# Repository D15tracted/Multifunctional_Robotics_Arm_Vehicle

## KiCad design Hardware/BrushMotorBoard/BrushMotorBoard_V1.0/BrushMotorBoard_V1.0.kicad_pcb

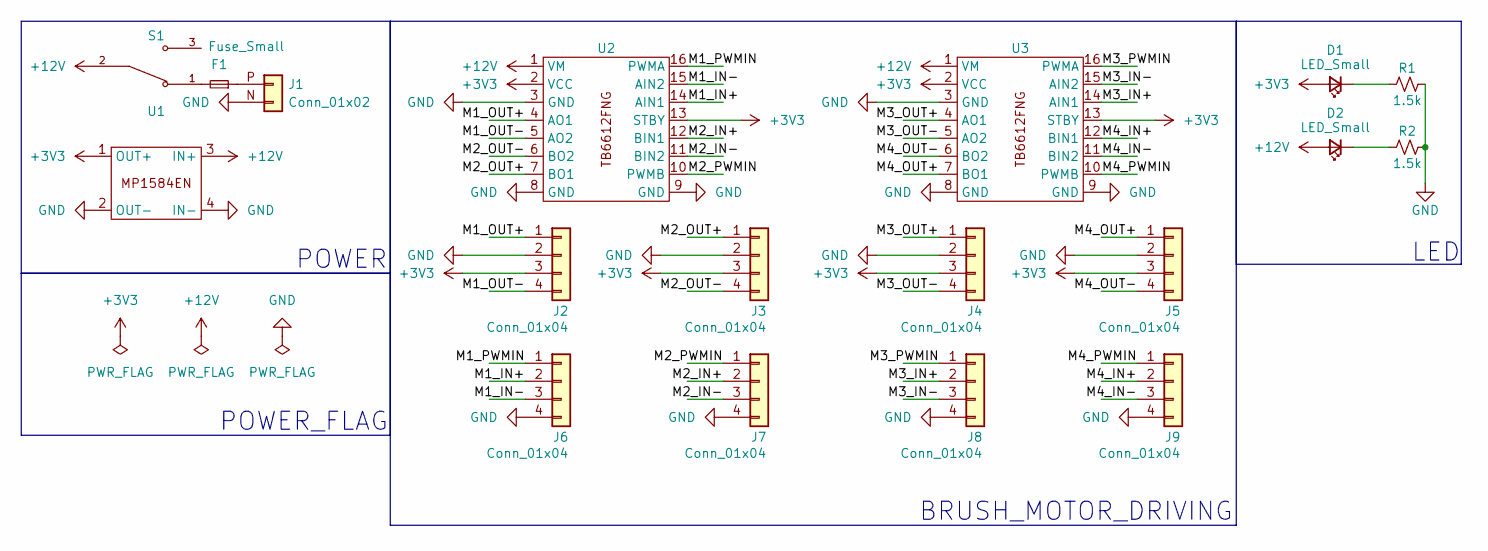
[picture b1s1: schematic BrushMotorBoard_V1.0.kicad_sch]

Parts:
D1, D2: LED_Small; LED_0805_2012Metric
F1: Fuse_Small; Fuse_Blade_ATO_directSolder
J1: Conn_01x02; AMASS_XT60-M
J2, J3, J4, J5, J6, J7, J8, J9: Conn_01x04; JST_XH_B4B-XH-A_1x04_P2.50mm_Vertical
R1, R2: 1.5k; R_0805_2012Metric
S1: SS12D10
U1: MP1584EN
U2, U3: TB6612FNG_Module

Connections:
+3V3: D1.2 (A), J2.3, J3.3, J4.3, J5.3, U1.1 (OUT+), U2.2 (VCC), U2.13 (STBY), U3.2 (VCC), U3.13 (STBY)
+12V: D2.2 (A), S1.2, U1.3 (IN+), U2.1 (VM), U3.1 (VM)
/M1_IN+: J6.2, U2.14 (AIN1)
/M1_IN-: J6.3, U2.15 (AIN2)
/M1_OUT+: J2.1, U2.4 (AO1)
/M1_OUT-: J2.4, U2.5 (AO2)
/M1_PWMIN: J6.1, U2.16 (PWMA)
/M2_IN+: J7.2, U2.12 (BIN1)
/M2_IN-: J7.3, U2.11 (BIN2)
/M2_OUT+: J3.1, U2.7 (BO1)
/M2_OUT-: J3.4, U2.6 (BO2)
/M2_PWMIN: J7.1, U2.10 (PWMB)
/M3_IN+: J8.2, U3.14 (AIN1)
/M3_IN-: J8.3, U3.15 (AIN2)
/M3_OUT+: J4.1, U3.4 (AO1)
/M3_OUT-: J4.4, U3.5 (AO2)
/M3_PWMIN: J8.1, U3.16 (PWMA)
/M4_IN+: J9.2, U3.12 (BIN1)
/M4_IN-: J9.3, U3.11 (BIN2)
/M4_OUT+: J5.1, U3.7 (BO1)
/M4_OUT-: J5.4, U3.6 (BO2)
/M4_PWMIN: J9.1, U3.10 (PWMB)
GND: J1.N (Pin_2), J2.2, J3.2, J4.2, J5.2, J6.4, J7.4, J8.4, J9.4, R1.2, R2.2, U1.2 (OUT-), U1.4 (IN-), U2.3 (GND), U2.8 (GND), U2.9 (GND), U3.3 (GND), U3.8 (GND), U3.9 (GND)
unnamed: D1.1 (K), R1.1
unnamed: D2.1 (K), R2.1
unnamed: F1.2, S1.1
unnamed: F1.1, J1.P (Pin_1)

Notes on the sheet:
POWER_FLAG
BRUSH_MOTOR_DRIVING
LED
POWER

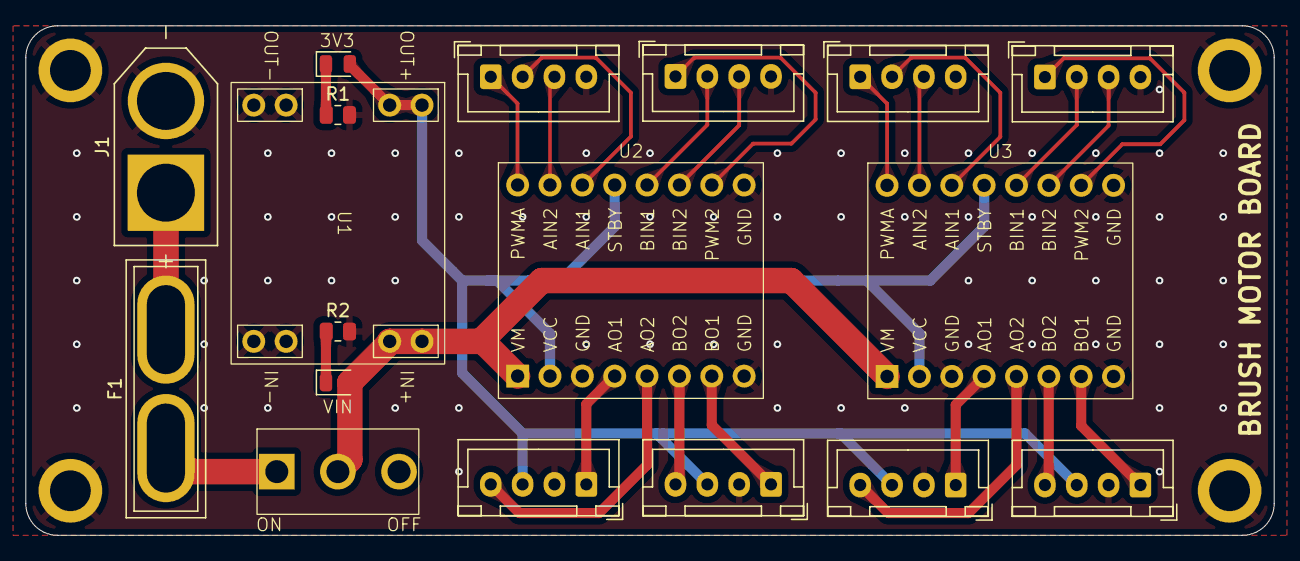
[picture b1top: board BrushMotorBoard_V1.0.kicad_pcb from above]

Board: 2 copper layers, 98.0 x 40.0 mm, 18 parts (0 on the bottom side), 27 nets.

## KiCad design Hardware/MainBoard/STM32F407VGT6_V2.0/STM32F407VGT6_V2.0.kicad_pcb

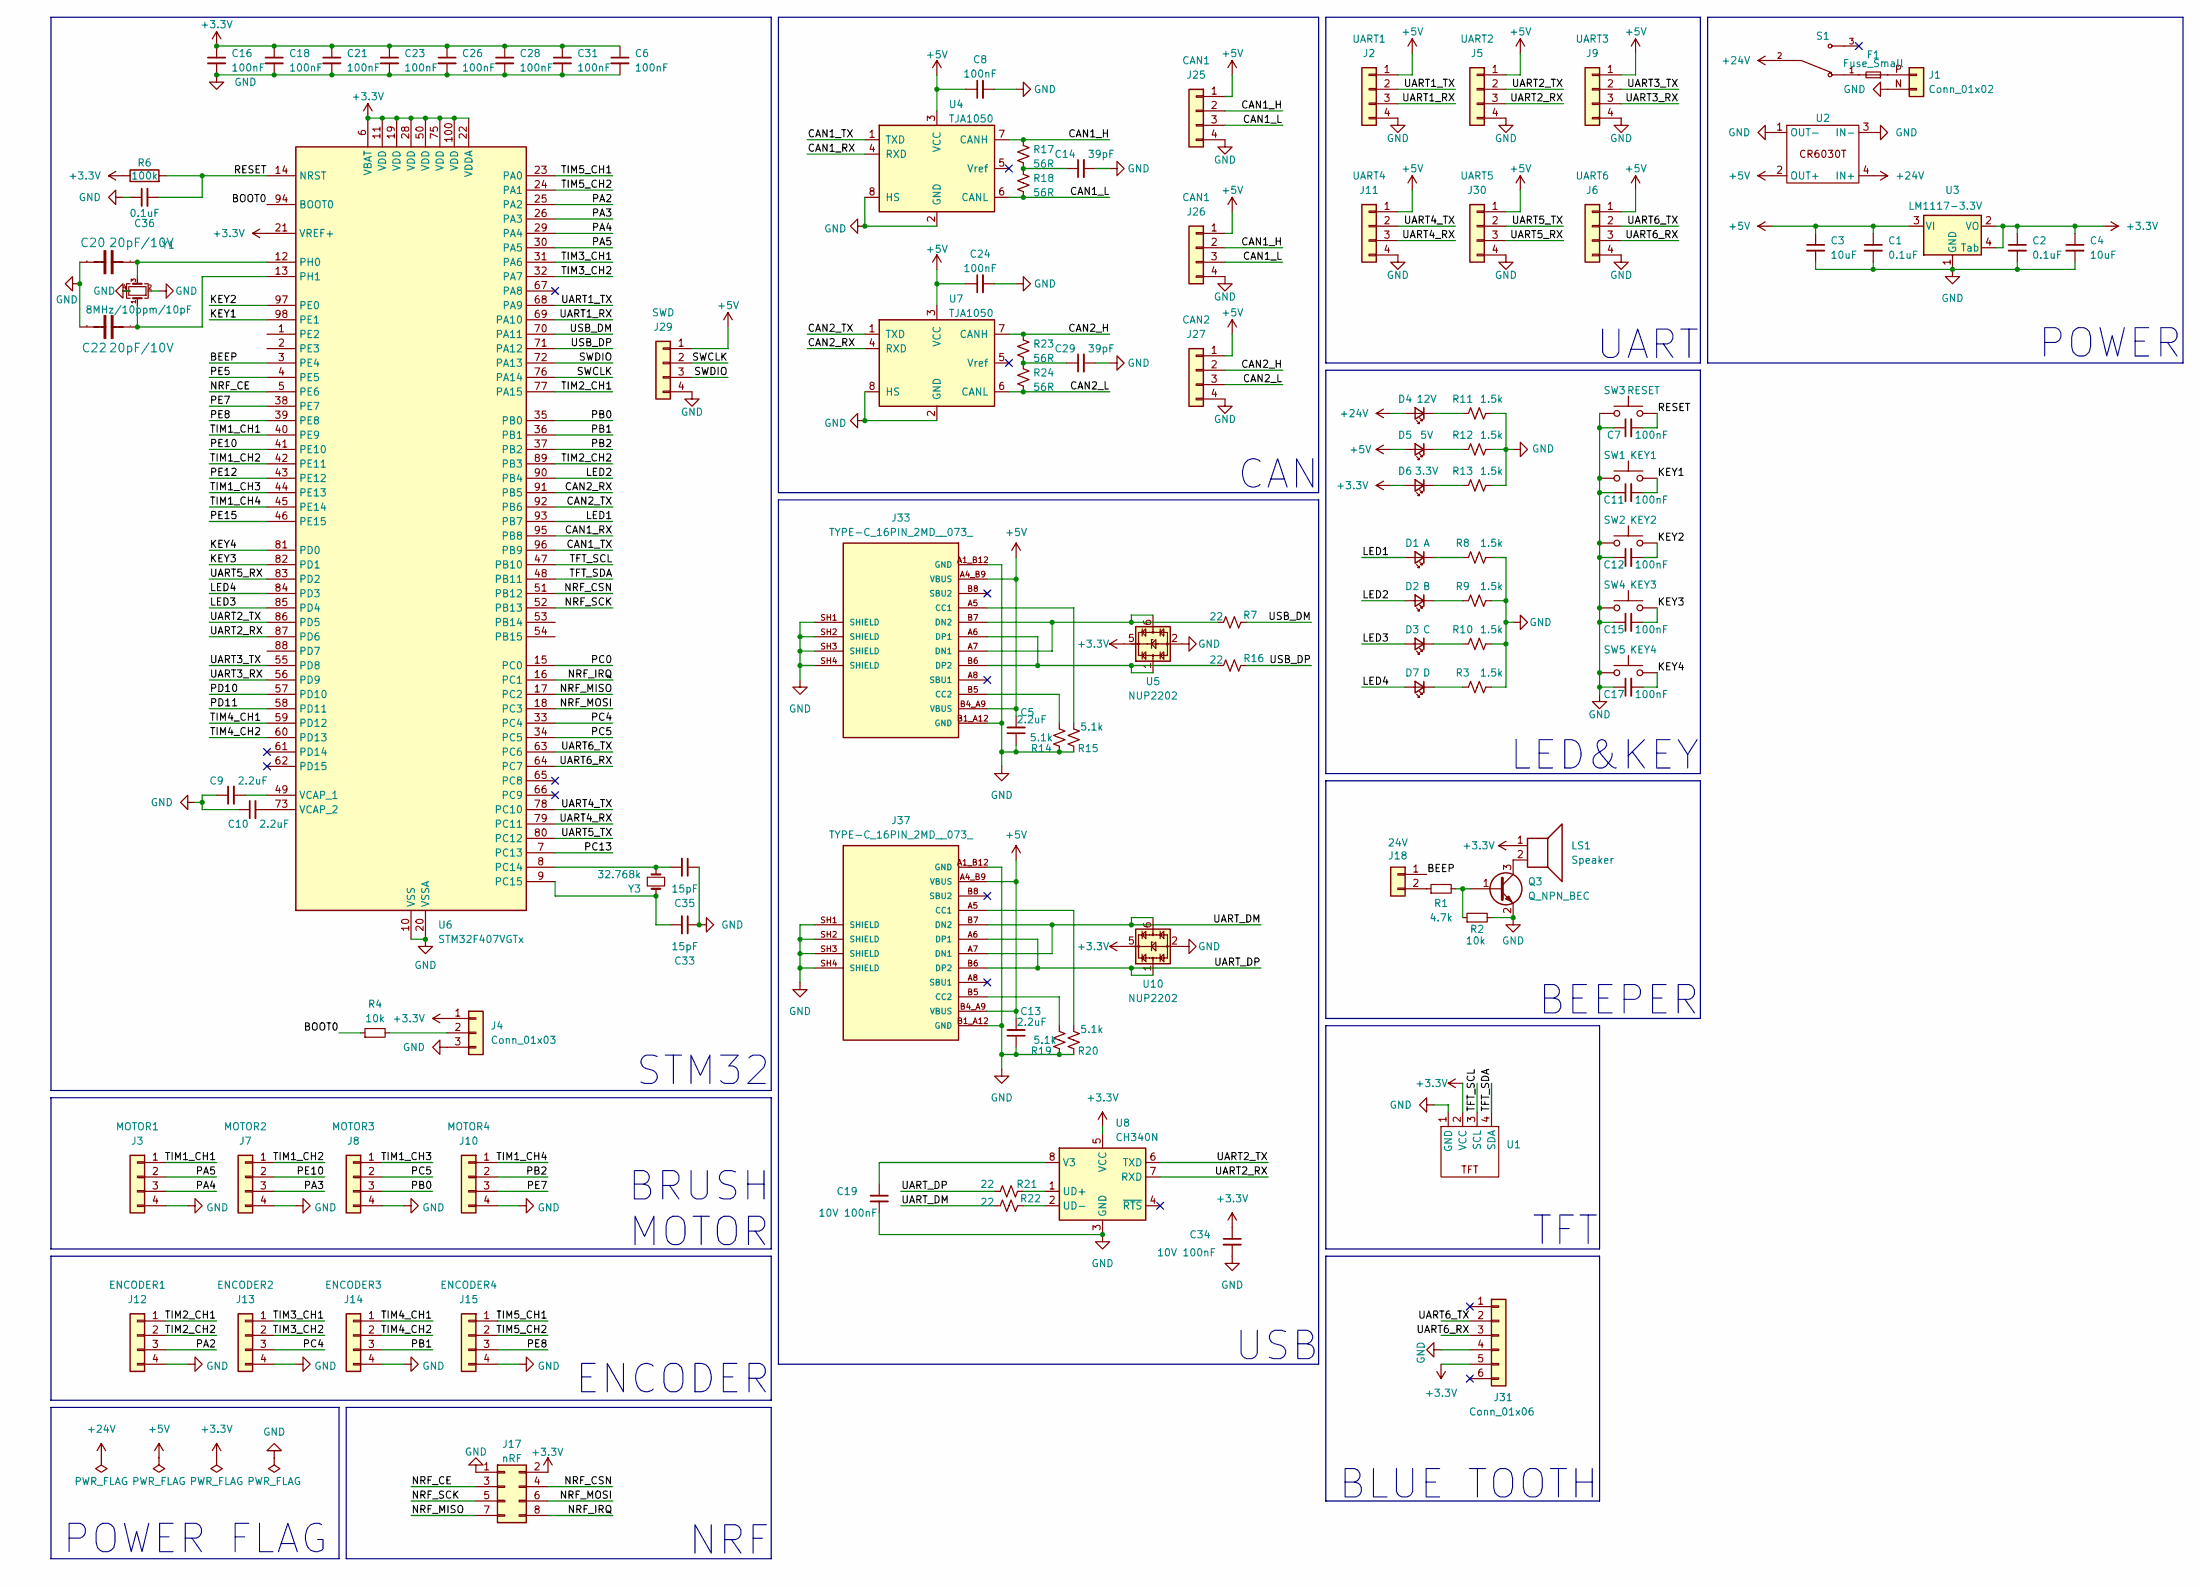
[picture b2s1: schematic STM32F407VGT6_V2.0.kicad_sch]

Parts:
C1, C2, C36: 0.1uF; C_0603_1608Metric
C3, C4: 10uF; C_0603_1608Metric
C5, C9, C10, C13: 2.2uF; C_0603_1608Metric
C6, C7, C8, C11, C12, C15, C16, C17, C18, C21, C23, C24, C26, C28, C31: 100nF; C_0603_1608Metric
C14, C29: 39pF; C_0603_1608Metric
C19, C34: 10V 100nF; C_0603_1608Metric
C20, C22: 20pF/10V; C_0603_1608Metric
C33, C35: 15pF; C_0603_1608Metric
D1: A; LED_0603_1608Metric
D2: B; LED_0603_1608Metric
D3: C; LED_0603_1608Metric
D4: 12V; LED_0603_1608Metric
D5: 5V; LED_0603_1608Metric
D6: 3.3V; LED_0603_1608Metric
D7: D; LED_0603_1608Metric
F1: Fuse_Small; Fuse_Blade_ATO_directSolder
J1: Conn_01x02; AMASS_XT60-M
J2: UART1; JST_XH_B4B-XH-A_1x04_P2.50mm_Vertical
J3: MOTOR1; JST_XH_B4B-XH-A_1x04_P2.50mm_Vertical
J4: Conn_01x03; PinHeader_1x03_P2.54mm_Vertical
J5: UART2; JST_XH_B4B-XH-A_1x04_P2.50mm_Vertical
J6: UART6; JST_XH_B4B-XH-A_1x04_P2.50mm_Vertical
J7: MOTOR2; JST_XH_B4B-XH-A_1x04_P2.50mm_Vertical
J8: MOTOR3; JST_XH_B4B-XH-A_1x04_P2.50mm_Vertical
J9: UART3; JST_XH_B4B-XH-A_1x04_P2.50mm_Vertical
J10: MOTOR4; JST_XH_B4B-XH-A_1x04_P2.50mm_Vertical
J11: UART4; JST_XH_B4B-XH-A_1x04_P2.50mm_Vertical
J12: ENCODER1; JST_XH_B4B-XH-A_1x04_P2.50mm_Vertical
J13: ENCODER2; JST_XH_B4B-XH-A_1x04_P2.50mm_Vertical
J14: ENCODER3; JST_XH_B4B-XH-A_1x04_P2.50mm_Vertical
J15: ENCODER4; JST_XH_B4B-XH-A_1x04_P2.50mm_Vertical
J17: nRF; PinHeader_2x04_P2.54mm_Vertical
J18: 24V; Conn1x02P
J25, J26: CAN1; JST_XH_B4B-XH-A_1x04_P2.50mm_Vertical
J27: CAN2; JST_XH_B4B-XH-A_1x04_P2.50mm_Vertical
J29: SWD; JST_XH_B4B-XH-A_1x04_P2.50mm_Vertical
J30: UART5; JST_XH_B4B-XH-A_1x04_P2.50mm_Vertical
J31: Conn_01x06; BLUE_TOOTH
J33, J37: TYPE-C_16PIN_2MD__073_; SHOUHAN_ TYPEC 16PIN; PARTREV A
LS1: Speaker; Beeper9mm
Q3: Q_NPN_BEC; SOT-23
R1: 4.7k; R_0603_1608Metric
R2, R4: 10k; R_0603_1608Metric
R3, R8, R9, R10, R11, R12, R13: 1.5k; R_0603_1608Metric
R6: 100k; R_0603_1608Metric
R7, R16, R21, R22: 22; R_0603_1608Metric
R14, R15, R19, R20: 5.1k; R_0603_1608Metric
R17, R18, R23, R24: 56R; R_0603_1608Metric
S1: SS12D10
SW1: KEY1; SW_Push
SW2: KEY2; SW_Push
SW3: RESET; SW_Push
SW4: KEY3; SW_Push
SW5: KEY4; SW_Push
U1: OLED_WithoutMountingHole
U2: CR6030T
U3: LM1117-3.3V; SOT-223
U4, U7: TJA1050; ISO1541D_SOIC-8
U5, U10: NUP2202; SOT-363_SC-70-6
U6: STM32F407VGTx; LQFP-100_14x14mm_P0.5mm
U8: CH340N; SOIC-8_5.3x6.2mm_P1.27mm
Y1: 8MHz/10ppm/10pF; Crystal_SMD_3225-4Pin_3.2x2.5mm
Y3: 32.768k; SMD-3215-2P

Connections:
+3.3V: C2.1, C4.1, C6.1, C16.1, C18.1, C21.1, C23.1, C26.1, C28.1, C31.1, C34.1, D6.2 (A), J4.1, J17.2, J31.5, LS1.1, R6.1, U1.2 (VCC), U3.2 (VO), U3.4 (Tab), U5.5, U6.6 (VBAT), U6.11 (VDD), U6.19 (VDD), U6.21 (VREF+), U6.22 (VDDA), U6.28 (VDD), U6.50 (VDD), U6.75 (VDD), U6.100 (VDD), U8.5 (VCC), U10.5
+5V: C1.1, C3.1, C5.2, C8.1, C13.2, C24.1, D5.2 (A), J2.1, J5.1, J6.1, J9.1, J11.1, J25.1, J26.1, J27.1, J29.1, J30.1, J33.A4_B9 (VBUS), J33.B4_A9 (VBUS), J37.A4_B9 (VBUS), J37.B4_A9 (VBUS), U2.2 (OUT+), U3.3 (VI), U4.3 (VCC), U7.3 (VCC)
+24V: D4.2 (A), S1.2, U2.4 (IN+)
/BEEP: J18.1, U6.3 (PE4)
/BOOT0: R4.1, U6.94 (BOOT0)
/CAN1_H: J25.2, J26.2, R17.1, U4.7 (CANH)
/CAN1_L: J25.3, J26.3, R18.2, U4.6 (CANL)
/CAN1_RX: U4.4 (RXD), U6.95 (PB8)
/CAN1_TX: U4.1 (TXD), U6.96 (PB9)
/CAN2_H: J27.2, R23.1, U7.7 (CANH)
/CAN2_L: J27.3, R24.2, U7.6 (CANL)
/CAN2_RX: U6.91 (PB5), U7.4 (RXD)
/CAN2_TX: U6.92 (PB6), U7.1 (TXD)
/KEY1: C11.2, SW1.2, U6.98 (PE1)
/KEY2: C12.2, SW2.2, U6.97 (PE0)
/KEY3: C15.2, SW4.2, U6.82 (PD1)
/KEY4: C17.2, SW5.2, U6.81 (PD0)
/LED1: D1.2 (A), U6.93 (PB7)
/LED2: D2.2 (A), U6.90 (PB4)
/LED3: D3.2 (A), U6.85 (PD4)
/LED4: D7.2 (A), U6.84 (PD3)
/NRF_CE: J17.3, U6.5 (PE6)
/NRF_CSN: J17.4, U6.51 (PB12)
/NRF_IRQ: J17.8, U6.16 (PC1)
/NRF_MISO: J17.7, U6.17 (PC2)
/NRF_MOSI: J17.6, U6.18 (PC3)
/NRF_SCK: J17.5, U6.52 (PB13)
/PA2: J12.3, U6.25 (PA2)
/PA3: J7.3, U6.26 (PA3)
/PA4: J3.3, U6.29 (PA4)
/PA5: J3.2, U6.30 (PA5)
/PB0: J8.3, U6.35 (PB0)
/PB1: J14.3, U6.36 (PB1)
/PB2: J10.2, U6.37 (PB2)
/PC0: U6.15 (PC0)
/PC4: J13.3, U6.33 (PC4)
/PC5: J8.2, U6.34 (PC5)
/PC13: U6.7 (PC13)
/PD10: U6.57 (PD10)
/PD11: U6.58 (PD11)
/PE5: U6.4 (PE5)
/PE7: J10.3, U6.38 (PE7)
/PE8: J15.3, U6.39 (PE8)
/PE10: J7.2, U6.41 (PE10)
/PE12: U6.43 (PE12)
/PE15: U6.46 (PE15)
/RESET: C7.2, C36.2, R6.2, SW3.2, U6.14 (NRST)
/SWCLK: J29.2, U6.76 (PA14)
/SWDIO: J29.3, U6.72 (PA13)
/TFT_SCL: U1.3 (SCL), U6.47 (PB10)
/TFT_SDA: U1.4 (SDA), U6.48 (PB11)
/TIM1_CH1: J3.1, U6.40 (PE9)
/TIM1_CH2: J7.1, U6.42 (PE11)
/TIM1_CH3: J8.1, U6.44 (PE13)
/TIM1_CH4: J10.1, U6.45 (PE14)
/TIM2_CH1: J12.1, U6.77 (PA15)
/TIM2_CH2: J12.2, U6.89 (PB3)
/TIM3_CH1: J13.1, U6.31 (PA6)
/TIM3_CH2: J13.2, U6.32 (PA7)
/TIM4_CH1: J14.1, U6.59 (PD12)
/TIM4_CH2: J14.2, U6.60 (PD13)
/TIM5_CH1: J15.1, U6.23 (PA0)
/TIM5_CH2: J15.2, U6.24 (PA1)
/UART1_RX: J2.3, U6.69 (PA10)
/UART1_TX: J2.2, U6.68 (PA9)
/UART2_RX: J5.3, U6.87 (PD6), U8.7 (RXD)
/UART2_TX: J5.2, U6.86 (PD5), U8.6 (TXD)
/UART3_RX: J9.3, U6.56 (PD9)
/UART3_TX: J9.2, U6.55 (PD8)
/UART4_RX: J11.3, U6.79 (PC11)
/UART4_TX: J11.2, U6.78 (PC10)
/UART5_RX: J30.3, U6.83 (PD2)
/UART5_TX: J30.2, U6.80 (PC12)
/UART6_RX: J6.3, J31.3, U6.64 (PC7)
/UART6_TX: J6.2, J31.2, U6.63 (PC6)
/UART_DM: J37.A7 (DN1), J37.B7 (DN2), R22.1, U10.6
/UART_DP: J37.A6 (DP1), J37.B6 (DP2), R21.1, U10.1
/USB_DM: R7.2, U6.70 (PA11)
/USB_DP: R16.2, U6.71 (PA12)
GND: C1.2, C2.2, C3.2, C4.2, C5.1, C6.2, C7.1, C8.2, C9.1, C10.1, C11.1, C12.1, C13.1, C14.2, C15.1, C16.2, C17.1, C18.2, C19.2, C20.1, C21.2, C22.1, C23.2, C24.2, C26.2, C28.2, C29.2, C31.2, C33.1, C34.2, C35.1, C36.1, J1.N (Pin_2), J2.4, J3.4, J4.3, J5.4, J6.4, J7.4, J8.4, J9.4, J10.4, J11.4, J12.4, J13.4, J14.4, J15.4, J17.1, J25.4, J26.4, J27.4, J29.4, J30.4, J31.4, J33.A1_B12 (GND), J33.B1_A12 (GND), J33.SH1 (SHIELD), J33.SH2 (SHIELD), J33.SH3 (SHIELD), J33.SH4 (SHIELD), J37.A1_B12 (GND), J37.B1_A12 (GND), J37.SH1 (SHIELD), J37.SH2 (SHIELD), J37.SH3 (SHIELD), J37.SH4 (SHIELD), Q3.2 (E), R2.2, R3.1, R8.1, R9.1, R10.1, R11.1, R12.1, R13.1, R14.2, R15.2, R19.2, R20.2, SW1.1, SW2.1, SW3.1, SW4.1, SW5.1, U1.1 (GND), U2.1 (OUT-), U2.3 (IN-), U3.1 (GND), U4.2 (GND), U4.8 (HS), U5.2, U6.10 (VSS), U6.20 (VSSA), U6.27 (VSS), U6.74 (VSS), U6.99 (VSS), U7.2 (GND), U7.8 (HS), U8.3 (GND), U10.2, Y1.2, Y1.4
unnamed: C14.1, R17.2, R18.1
unnamed: C29.1, R23.2, R24.1
unnamed: D1.1 (K), R8.2
unnamed: D2.1 (K), R9.2
unnamed: D3.1 (K), R10.2
unnamed: D4.1 (K), R11.2
unnamed: D5.1 (K), R12.2
unnamed: D6.1 (K), R13.2
unnamed: D7.1 (K), R3.2
unnamed: F1.2, S1.1
unnamed: F1.1, J1.P (Pin_1)
unnamed: J4.2, R4.2
unnamed: J18.2, R1.1
unnamed: J33.A5 (CC1), R15.1
unnamed: J33.B5 (CC2), R14.1
unnamed: J33.A7 (DN1), J33.B7 (DN2), R7.1, U5.6
unnamed: J33.A6 (DP1), J33.B6 (DP2), R16.1, U5.1
unnamed: J37.A5 (CC1), R20.1
unnamed: J37.B5 (CC2), R19.1
unnamed: Q3.1 (B), R1.2, R2.1
unnamed: LS1.2, Q3.3 (C)
unnamed: C35.2, U6.8 (PC14), Y3.1
unnamed: C33.2, U6.9 (PC15), Y3.2
unnamed: C20.2, U6.12 (PH0), Y1.3
unnamed: C22.2, U6.13 (PH1), Y1.1
unnamed: C9.2, U6.49 (VCAP_1)
unnamed: C10.2, U6.73 (VCAP_2)
unnamed: R21.2, U8.1 (UD+)
unnamed: R22.2, U8.2 (UD-)
unnamed: C19.1, U8.8 (V3)

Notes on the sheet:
UART
LED&KEY
USB
POWER
POWER FLAG
BLUE TOOTH
TFT
BEEPER
NRF
CAN
BRUSH MOTOR
ENCODER
STM32

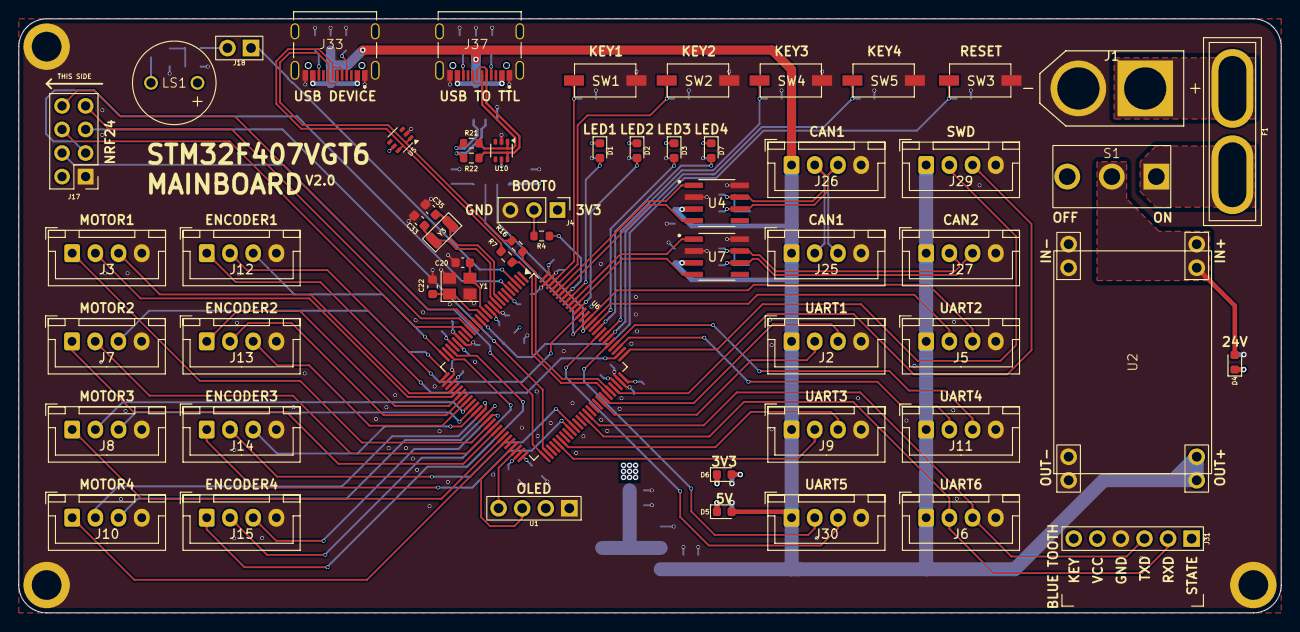
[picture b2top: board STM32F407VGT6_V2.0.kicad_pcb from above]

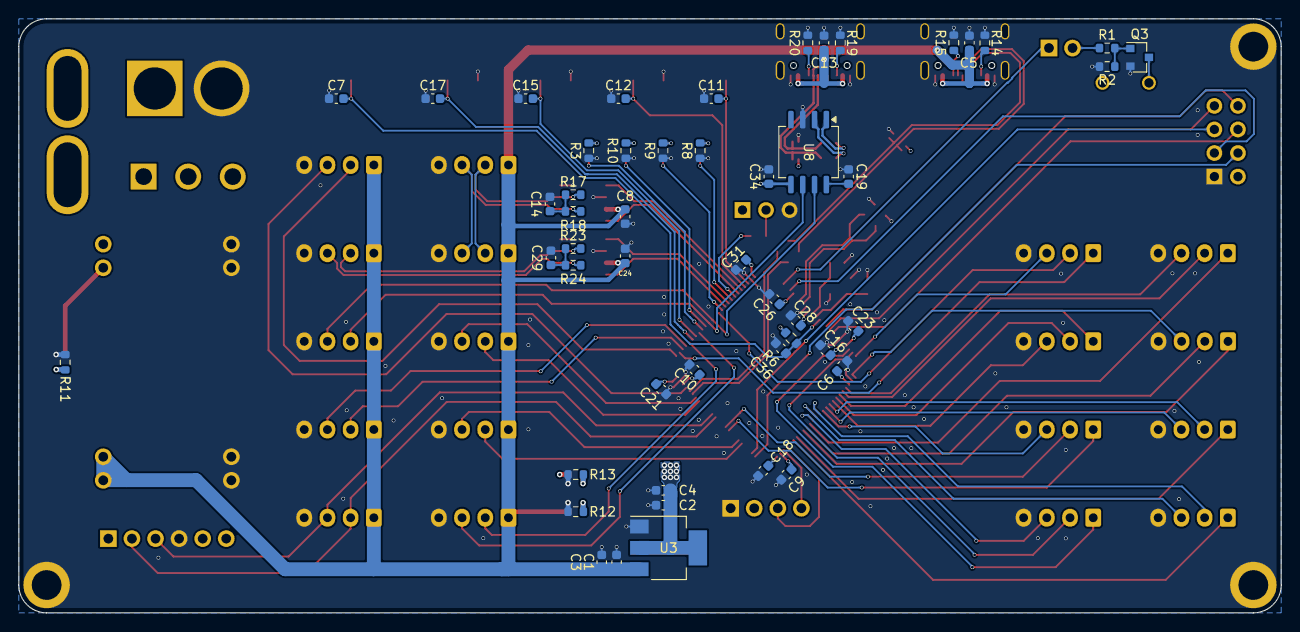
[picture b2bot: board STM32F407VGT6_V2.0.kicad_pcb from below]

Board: 4 copper layers, 136.0 x 64.0 mm, 107 parts (49 on the bottom side), 103 nets.

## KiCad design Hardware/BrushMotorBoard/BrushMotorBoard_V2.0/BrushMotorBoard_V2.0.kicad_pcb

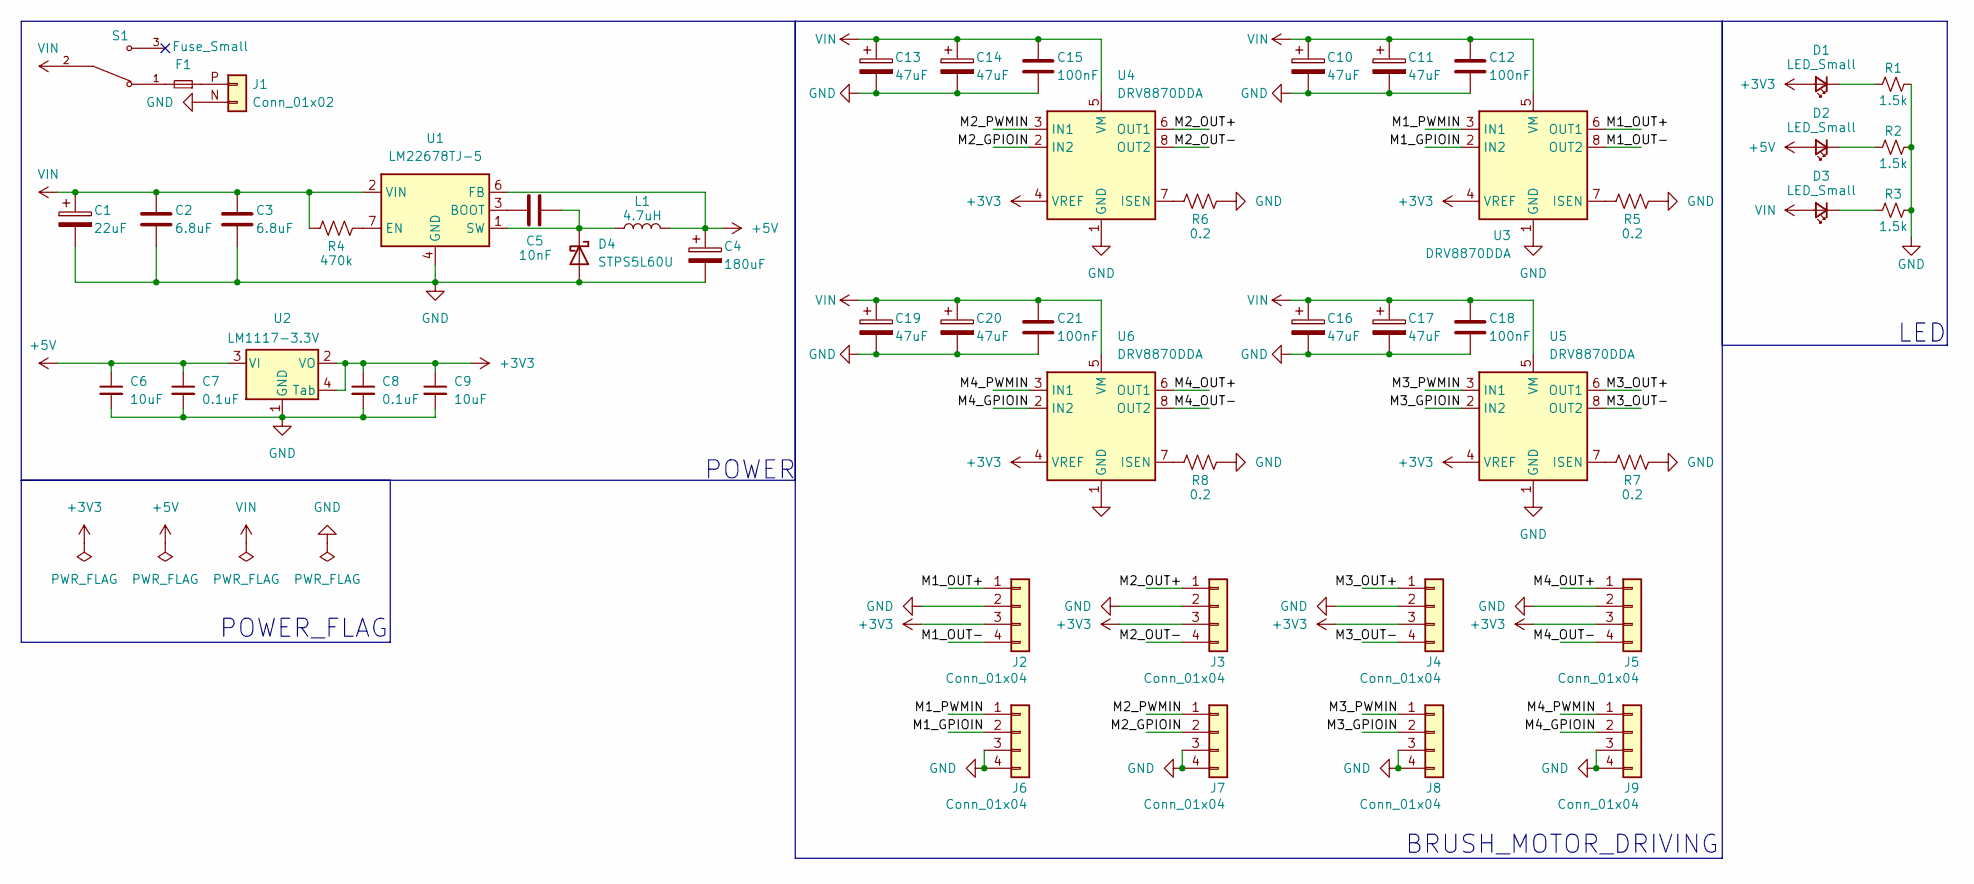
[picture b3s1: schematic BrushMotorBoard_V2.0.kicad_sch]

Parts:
C1: 22uF; CP_Elec_6.3x7.7
C2, C3: 6.8uF; C_1210_3225Metric
C4: 180uF; CP_Elec_6.3x7.7
C5: 10nF; C_0603_1608Metric
C6, C9: 10uF; C_0603_1608Metric
C7, C8: 0.1uF; C_0603_1608Metric
C10, C11, C13, C14, C16, C17, C19, C20: 47uF; CP_Elec_6.3x5.4
C12, C15, C18, C21: 100nF; C_0603_1608Metric
D1, D2, D3: LED_Small; LED_0603_1608Metric
D4: STPS5L60U; D_SMB
F1: Fuse_Small; Fuse_Blade_ATO_directSolder
J1: Conn_01x02; AMASS_XT60-M
J2, J3, J4, J5, J6, J7, J8, J9: Conn_01x04; JST_XH_B4B-XH-A_1x04_P2.50mm_Vertical
L1: 4.7uH; L_Vishay_IHLP-2525
R1, R2, R3: 1.5k; R_0603_1608Metric
R4: 470k; R_1210_3225Metric
R5, R6, R7, R8: 0.2; R_0603_1608Metric
S1: SS12D10
U1: LM22678TJ-5; TO-263-7_TabPin8
U2: LM1117-3.3V; SOT-223
U3, U4, U5, U6: DRV8870DDA; Texas_HTSOP-8-1EP_3.9x4.9mm_P1.27mm_EP2.95x4.9mm_Mask2.4x3.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

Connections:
+3V3: C8.1, C9.1, D1.2 (A), J2.3, J3.3, J4.3, J5.3, U2.2 (VO), U2.4 (Tab), U3.4 (VREF), U4.4 (VREF), U5.4 (VREF), U6.4 (VREF)
+5V: C4.1, C6.1, C7.1, D2.2 (A), L1.2, U1.6 (FB), U2.3 (VI)
/M1_GPIOIN: J6.2, U3.2 (IN2)
/M1_OUT+: J2.1, U3.6 (OUT1)
/M1_OUT-: J2.4, U3.8 (OUT2)
/M1_PWMIN: J6.1, U3.3 (IN1)
/M2_GPIOIN: J7.2, U4.2 (IN2)
/M2_OUT+: J3.1, U4.6 (OUT1)
/M2_OUT-: J3.4, U4.8 (OUT2)
/M2_PWMIN: J7.1, U4.3 (IN1)
/M3_GPIOIN: J8.2, U5.2 (IN2)
/M3_OUT+: J4.1, U5.6 (OUT1)
/M3_OUT-: J4.4, U5.8 (OUT2)
/M3_PWMIN: J8.1, U5.3 (IN1)
/M4_GPIOIN: J9.2, U6.2 (IN2)
/M4_OUT+: J5.1, U6.6 (OUT1)
/M4_OUT-: J5.4, U6.8 (OUT2)
/M4_PWMIN: J9.1, U6.3 (IN1)
GND: C1.2, C2.2, C3.2, C4.2, C6.2, C7.2, C8.2, C9.2, C10.2, C11.2, C12.2, C13.2, C14.2, C15.2, C16.2, C17.2, C18.2, C19.2, C20.2, C21.2, D4.2 (A), J1.N (Pin_2), J2.2, J3.2, J4.2, J5.2, J6.3, J6.4, J7.3, J7.4, J8.3, J8.4, J9.3, J9.4, R1.2, R2.2, R3.2, R5.1, R6.1, R7.1, R8.1, U1.4 (GND), U1.8 (GND), U2.1 (GND), U3.1 (GND), U3.9 (GND), U4.1 (GND), U4.9 (GND), U5.1 (GND), U5.9 (GND), U6.1 (GND), U6.9 (GND)
unnamed: D1.1 (K), R1.1
unnamed: D2.1 (K), R2.1
unnamed: D3.1 (K), R3.1
unnamed: C5.2, D4.1 (K), L1.1, U1.1 (SW)
unnamed: F1.2, S1.1
unnamed: F1.1, J1.P (Pin_1)
unnamed: C5.1, U1.3 (BOOT)
unnamed: R4.1, U1.7 (EN)
unnamed: R5.2, U3.7 (ISEN)
unnamed: R6.2, U4.7 (ISEN)
unnamed: R7.2, U5.7 (ISEN)
unnamed: R8.2, U6.7 (ISEN)
VIN: C1.1, C2.1, C3.1, C10.1, C11.1, C12.1, C13.1, C14.1, C15.1, C16.1, C17.1, C18.1, C19.1, C20.1, C21.1, D3.2 (A), R4.2, S1.2, U1.2 (VIN), U3.5 (VM), U4.5 (VM), U5.5 (VM), U6.5 (VM)

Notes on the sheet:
POWER_FLAG
BRUSH_MOTOR_DRIVING
LED
POWER

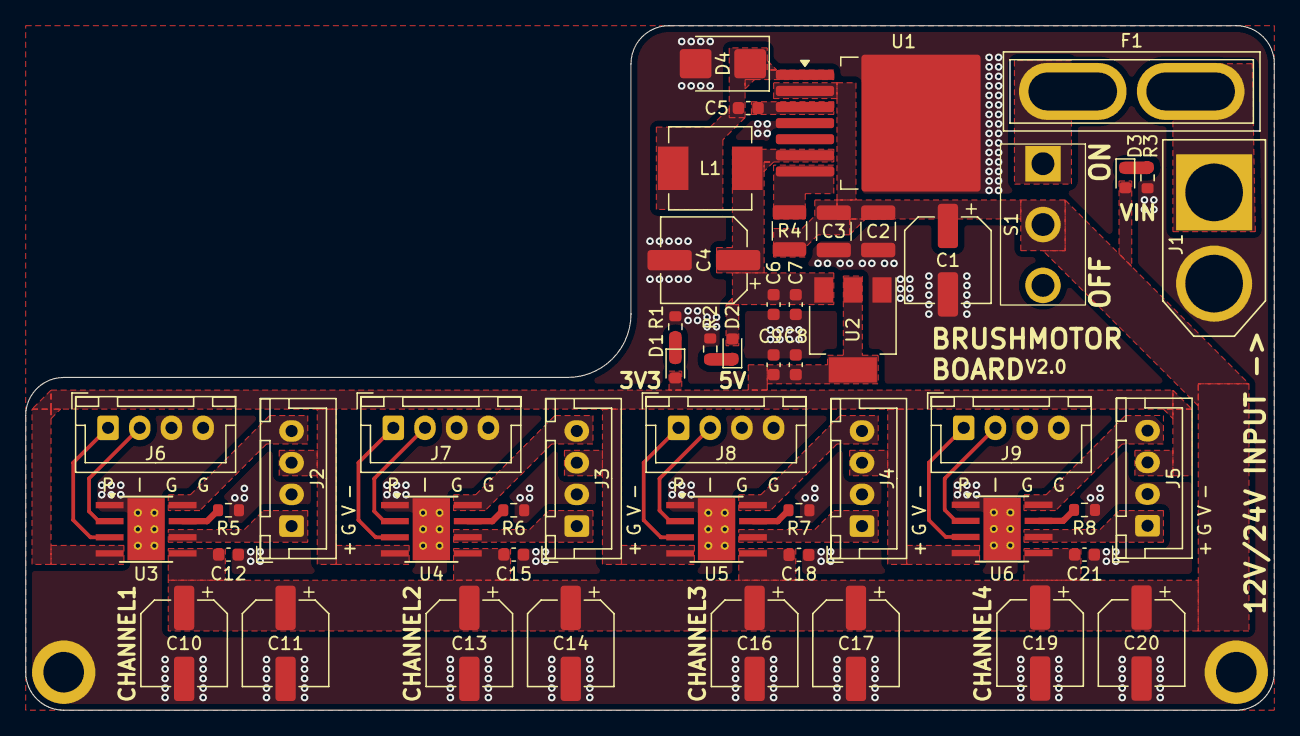
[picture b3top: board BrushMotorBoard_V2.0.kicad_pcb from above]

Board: 2 copper layers, 98.5 x 54.0 mm, 51 parts (0 on the bottom side), 32 nets.

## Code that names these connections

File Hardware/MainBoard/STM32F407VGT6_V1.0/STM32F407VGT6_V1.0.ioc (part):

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Mcu.Name=STM32F407V(E-G)Tx
Mcu.Package=LQFP100
Mcu.UserName=STM32F407VGTx
PA0-WKUP.Signal=S_TIM5_CH1
PA1.Signal=S_TIM5_CH2
PA10.Signal=USART1_RX
PA13.Mode=Serial_Wire
PA13.Signal=SYS_JTMS-SWDIO
PA14.Mode=Serial_Wire
PA14.Signal=SYS_JTCK-SWCLK
PA15.Signal=S_TIM2_CH1_ETR
PA2.Signal=GPIO_Output
PA3.Signal=GPIO_Output
PA4.Signal=GPIO_Output
PA5.Signal=GPIO_Output
PA6.Signal=S_TIM3_CH1
PA7.Signal=S_TIM3_CH2
PA9.Signal=USART1_TX
PB0.Signal=GPIO_Output
PB1.Signal=GPIO_Output
PB10.Signal=SPI2_SCK
PB11.Signal=GPIO_Output
PB12.Mode=CAN_Activate
PB12.Signal=CAN2_RX
PB13.Mode=CAN_Activate
PB13.Signal=CAN2_TX
PB14.Signal=USB_OTG_HS_DM
PB15.Signal=USB_OTG_HS_DP
PB3.Signal=S_TIM2_CH2
PB4.Signal=GPIO_Input
PB5.Signal=GPIO_Input
PB6.Signal=I2C1_SCL
PB7.Signal=I2C1_SDA
PB8.Mode=CAN_Activate
PB8.Signal=CAN1_RX
PB9.Mode=CAN_Activate
PB9.Signal=CAN1_TX
PC0.Signal=GPIO_Output
PC1.Signal=GPIO_Output
PC10.Signal=UART4_TX
PC11.Signal=UART4_RX
PC12.Signal=UART5_TX
PC13-ANTI_TAMP.Signal=GPIO_Output
PC14-OSC32_IN.Mode=LSE-External-Oscillator
PC14-OSC32_IN.Signal=RCC_OSC32_IN
PC15-OSC32_OUT.Mode=LSE-External-Oscillator
PC15-OSC32_OUT.Signal=RCC_OSC32_OUT
PC2.Signal=SPI2_MISO
PC3.Signal=SPI2_MOSI
PC4.Signal=GPIO_Output
PC5.Signal=GPIO_Output
PC6.Signal=USART6_TX
PC7.Signal=USART6_RX
PD0.Signal=GPIO_Output
PD1.Signal=GPIO_Output
PD10.Signal=GPIO_Output
PD12.Signal=S_TIM4_CH1
PD13.Signal=S_TIM4_CH2
PD2.Signal=UART5_RX
PD3.Signal=GPIO_Output
PD4.Signal=GPIO_Output
PD5.Signal=USART2_TX
PD6.Signal=USART2_RX
PD8.Signal=USART3_TX
PD9.Signal=USART3_RX
PE0.Signal=GPIO_Input
PE1.Signal=GPIO_Input
PE10.Signal=GPIO_Output
PE11.Signal=S_TIM1_CH2
PE12.Signal=GPIO_Output
PE13.Signal=S_TIM1_CH3
PE14.Signal=S_TIM1_CH4
PE15.Signal=GPIO_Output
PE2.Signal=GPIO_Output
PE3.Signal=GPIO_Output
PE4.Signal=GPIO_Output
PE5.Signal=GPIO_Output
PE6.Signal=GPIO_Output
PE7.Signal=GPIO_Output
PE8.Signal=GPIO_Output
PE9.Signal=S_TIM1_CH1
PH0-OSC_IN.Mode=HSE-External-Oscillator
PH0-OSC_IN.Signal=RCC_OSC_IN
PH1-OSC_OUT.Mode=HSE-External-Oscillator
PH1-OSC_OUT.Signal=RCC_OSC_OUT
RCC.HSE_VALUE=25000000
RCC.SYSCLKFreq_VALUE=16000000
board=custom

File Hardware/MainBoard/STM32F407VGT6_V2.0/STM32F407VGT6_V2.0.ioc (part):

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Mcu.Name=STM32F407V(E-G)Tx
Mcu.Package=LQFP100
Mcu.UserName=STM32F407VGTx
PA0-WKUP.Signal=S_TIM5_CH1
PA1.Signal=S_TIM5_CH2
PA10.Mode=Asynchronous
PA10.Signal=USART1_RX
PA11.Mode=Device_Only
PA11.Signal=USB_OTG_FS_DM
PA12.Mode=Device_Only
PA12.Signal=USB_OTG_FS_DP
PA13.Mode=Serial_Wire
PA13.Signal=SYS_JTMS-SWDIO
PA14.Mode=Serial_Wire
PA14.Signal=SYS_JTCK-SWCLK
PA15.Signal=S_TIM2_CH1_ETR
PA6.Signal=S_TIM3_CH1
PA7.Signal=S_TIM3_CH2
PA9.Mode=Asynchronous
PA9.Signal=USART1_TX
PB10.Mode=I2C
PB10.Signal=I2C2_SCL
PB11.Mode=I2C
PB11.Signal=I2C2_SDA
PB12.Mode=NSS_Signal_Hard_Input
PB12.Signal=SPI2_NSS
PB13.Mode=Full_Duplex_Master
PB13.Signal=SPI2_SCK
PB3.Signal=S_TIM2_CH2
PB5.Mode=CAN_Activate
PB5.Signal=CAN2_RX
PB6.Mode=CAN_Activate
PB6.Signal=CAN2_TX
PB8.Mode=CAN_Activate
PB8.Signal=CAN1_RX
PB9.Mode=CAN_Activate
PB9.Signal=CAN1_TX
PC10.Mode=Asynchronous
PC10.Signal=UART4_TX
PC11.Mode=Asynchronous
PC11.Signal=UART4_RX
PC12.Mode=Asynchronous
PC12.Signal=UART5_TX
PC14-OSC32_IN.Mode=LSE-External-Oscillator
PC14-OSC32_IN.Signal=RCC_OSC32_IN
PC15-OSC32_OUT.Mode=LSE-External-Oscillator
PC15-OSC32_OUT.Signal=RCC_OSC32_OUT
PC2.Mode=Full_Duplex_Master
PC2.Signal=SPI2_MISO
PC3.Mode=Full_Duplex_Master
PC3.Signal=SPI2_MOSI
PC6.Mode=Asynchronous
PC6.Signal=USART6_TX
PC7.Mode=Asynchronous
PC7.Signal=USART6_RX
PD12.Signal=S_TIM4_CH1
PD13.Signal=S_TIM4_CH2
PD2.Mode=Asynchronous
PD2.Signal=UART5_RX
PD5.Mode=Asynchronous
PD5.Signal=USART2_TX
PD6.Mode=Asynchronous
PD6.Signal=USART2_RX
PD8.Mode=Asynchronous
PD8.Signal=USART3_TX
PD9.Mode=Asynchronous
PD9.Signal=USART3_RX
PE11.Signal=S_TIM1_CH2
PE13.Signal=S_TIM1_CH3
PE14.Signal=S_TIM1_CH4
PE9.Signal=S_TIM1_CH1
PH0-OSC_IN.Mode=HSE-External-Oscillator
PH0-OSC_IN.Signal=RCC_OSC_IN
PH1-OSC_OUT.Mode=HSE-External-Oscillator
PH1-OSC_OUT.Signal=RCC_OSC_OUT
RCC.HSE_VALUE=25000000
RCC.SYSCLKFreq_VALUE=16000000
board=custom

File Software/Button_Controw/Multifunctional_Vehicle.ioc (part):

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Mcu.Name=STM32F407V(E-G)Tx
Mcu.Package=LQFP100
Mcu.UserName=STM32F407VGTx
PA13.Mode=Serial_Wire
PA13.Signal=SYS_JTMS-SWDIO
PA14.Mode=Serial_Wire
PA14.Signal=SYS_JTCK-SWCLK
PB4.GPIOParameters=GPIO_PuPd,GPIO_Label
PB4.GPIO_Label=KEY4
PB4.GPIO_PuPd=GPIO_PULLUP
PB4.Signal=GPIO_Input
PB5.GPIOParameters=GPIO_PuPd,GPIO_Label
PB5.GPIO_Label=KEY3
PB5.GPIO_PuPd=GPIO_PULLUP
PB5.Signal=GPIO_Input
PB6.GPIOParameters=GPIO_Speed,GPIO_PuPd,GPIO_ModeDefaultOutputPP
PB6.GPIO_ModeDefaultOutputPP=GPIO_MODE_OUTPUT_OD
PB6.GPIO_PuPd=GPIO_NOPULL
PB6.GPIO_Speed=GPIO_SPEED_FREQ_VERY_HIGH
PB6.Signal=GPIO_Output
PB7.GPIOParameters=GPIO_Speed,GPIO_PuPd,GPIO_ModeDefaultOutputPP
PB7.GPIO_ModeDefaultOutputPP=GPIO_MODE_OUTPUT_OD
PB7.GPIO_PuPd=GPIO_NOPULL
PB7.GPIO_Speed=GPIO_SPEED_FREQ_VERY_HIGH
PB7.Signal=GPIO_Output
PB8.Mode=CAN_Activate
PB8.Signal=CAN1_RX
PB9.Mode=CAN_Activate
PB9.Signal=CAN1_TX
PC12.Mode=Asynchronous
PC12.Signal=UART5_TX
PC14-OSC32_IN.Mode=LSE-External-Oscillator
PC14-OSC32_IN.Signal=RCC_OSC32_IN
PC15-OSC32_OUT.Mode=LSE-External-Oscillator
PC15-OSC32_OUT.Signal=RCC_OSC32_OUT
PD0.GPIOParameters=GPIO_Label
PD0.GPIO_Label=LED4
PD0.Signal=GPIO_Output
PD1.GPIOParameters=GPIO_Label
PD1.GPIO_Label=LED3
PD1.Signal=GPIO_Output
PD2.Mode=Asynchronous
PD2.Signal=UART5_RX
PD3.GPIOParameters=GPIO_Label
PD3.GPIO_Label=LED2
PD3.Signal=GPIO_Output
PD4.GPIOParameters=GPIO_Label
PD4.GPIO_Label=LED1
PD4.Signal=GPIO_Output
PE0.GPIOParameters=GPIO_PuPd,GPIO_Label
PE0.GPIO_Label=KEY2
PE0.GPIO_PuPd=GPIO_PULLUP
PE0.Signal=GPIO_Input
PE1.GPIOParameters=GPIO_PuPd,GPIO_Label
PE1.GPIO_Label=KEY1
PE1.GPIO_PuPd=GPIO_PULLUP
PE1.Signal=GPIO_Input
PH0-OSC_IN.Mode=HSE-External-Oscillator
PH0-OSC_IN.Signal=RCC_OSC_IN
PH1-OSC_OUT.Mode=HSE-External-Oscillator
PH1-OSC_OUT.Signal=RCC_OSC_OUT
RCC.HSE_VALUE=8000000
RCC.SYSCLKFreq_VALUE=168000000
RCC.SYSCLKSource=RCC_SYSCLKSOURCE_PLLCLK
board=custom
